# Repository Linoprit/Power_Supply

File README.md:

# Power_Supply
Code and schematics to build an analog power supply

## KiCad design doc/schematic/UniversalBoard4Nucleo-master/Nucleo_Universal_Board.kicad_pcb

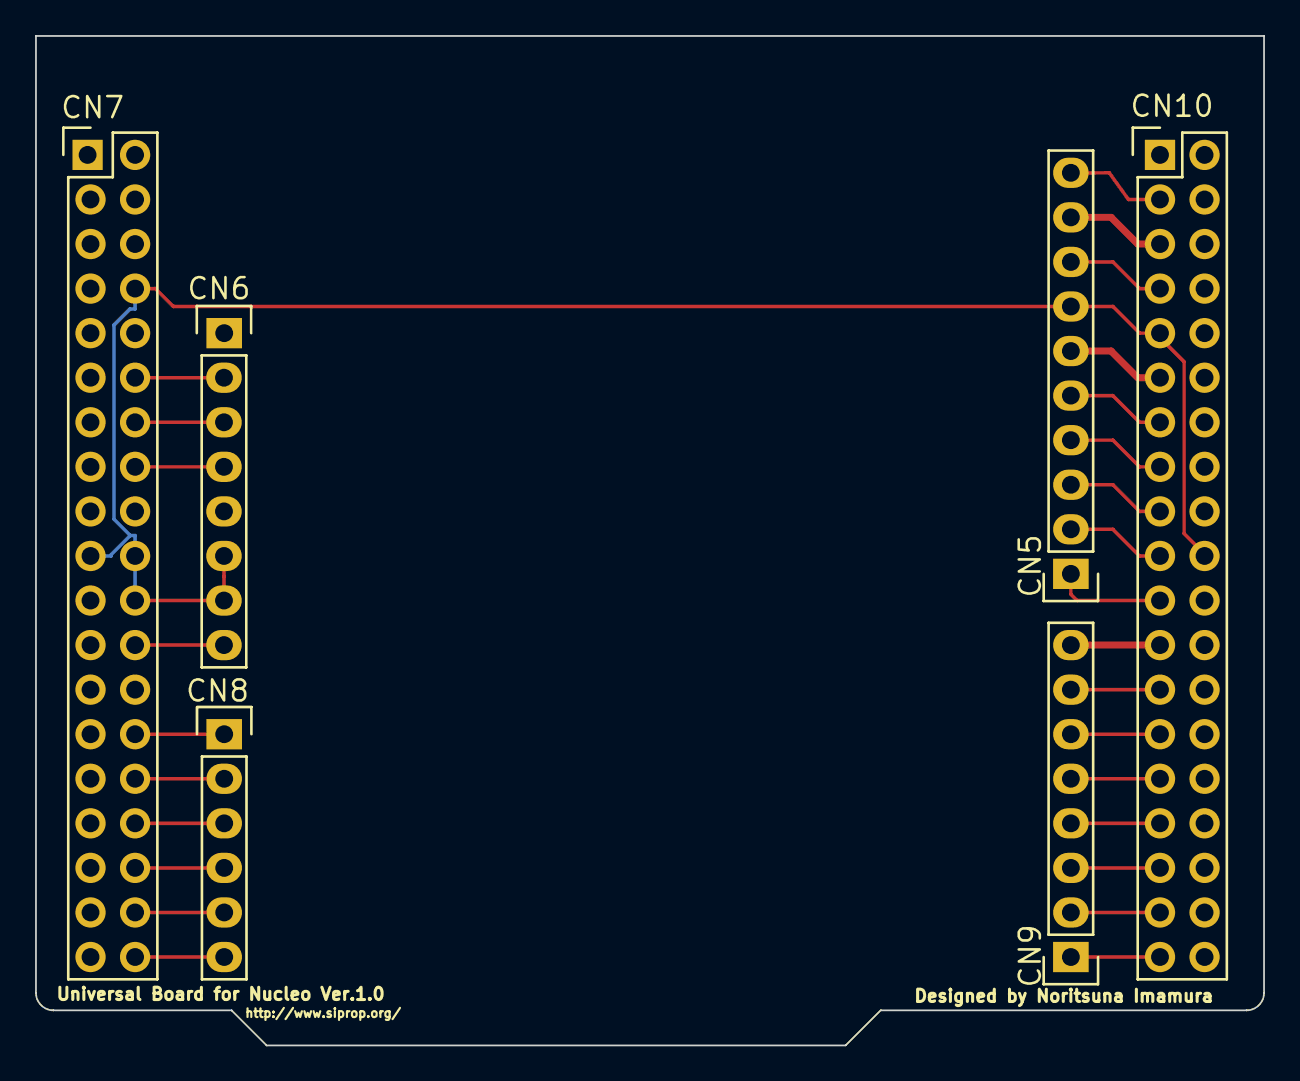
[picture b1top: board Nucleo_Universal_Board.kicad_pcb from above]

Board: 2 copper layers, 70.0 x 57.5 mm, 6 parts (0 on the bottom side), 28 nets.

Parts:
CN5: CONN_01X10; Pin_Header_Straight_1x10
CN6, CN9: CONN_01X08; Pin_Header_Straight_1x08
CN7, CN10: CONN_02X19; Pin_Header_Straight_2x19
CN8: CONN_01X06; Pin_Header_Straight_1x06

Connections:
/+3V3: CN6.4, CN7.16
/AVDD: CN5.8, CN10.7
/GND: CN5.7, CN6.6, CN6.7, CN7.8, CN7.19, CN7.20, CN7.22, CN10.9, CN10.20
/IOREF: CN6.2, CN7.12
/PA0: CN7.28, CN8.1
/PA1: CN7.30, CN8.2
/PA2: CN9.2, CN10.35
/PA3: CN9.1, CN10.37
/PA4: CN7.32, CN8.3
/PA5: CN5.6, CN10.11
/PA6: CN5.5, CN10.13
/PA7: CN5.4, CN10.15
/PA8: CN9.8, CN10.23
/PA9: CN5.1, CN10.21
/PA10: CN9.3, CN10.33
/PB0: CN7.34, CN8.4
/PB3: CN9.4, CN10.31
/PB4: CN9.6, CN10.27
/PB5: CN9.5, CN10.29
/PB6: CN5.3, CN10.17
/PB8: CN5.10, CN10.3
/PB9: CN5.9, CN10.5
/PB10: CN9.7, CN10.25
/PC0: CN7.38, CN8.6
/PC1: CN7.36, CN8.5
/PC7: CN5.2, CN10.19
/RES: CN6.3, CN7.14
/VIN: CN6.8, CN7.24

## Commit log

2016-12-21 Import aus open_radio
2016-12-21 eclipse project files added
2016-12-31 Comm_Layer working.
2017-01-02 Rotary Encoder I2C working.
2017-01-07 Rotary_Encoder finished.
2017-01-09 Char LCD Device finished with test.
2017-04-02 Value Class invented ;-)
2017-04-07 DAC Grundfunktion arbeitet
2017-12-03 Umstellung auf CubeMX
2017-12-18 LCD made nonblocking.
2017-12-21 Zwischenstand Measurement Klassen und ADC Klassen sind am Entstehen.
2018-01-01 Measurements and measurement-display first version finished.
2018-03-24 Outputting voltage works. Measurement voltage works, not yet calibrated.
2020-04-26 initial with new structure
2020-04-26 removed old dirs
2020-05-02 removed old dirs.
2020-05-14 NonVolatileData Class finished.
2020-05-15 VolatileData implemented.
2020-05-24 Display working, setting Rshunt still buggy.
2020-06-07 Rshunt adjustment is working.
2020-06-21 Umstellung auf ST CubeIDE
2020-08-29 Controller works. EEPROM and Temperature to do.
2020-11-21 Sync before testing USB-serial
2020-11-21 USB und commandLine is running.
2020-11-29 First full functioning.
